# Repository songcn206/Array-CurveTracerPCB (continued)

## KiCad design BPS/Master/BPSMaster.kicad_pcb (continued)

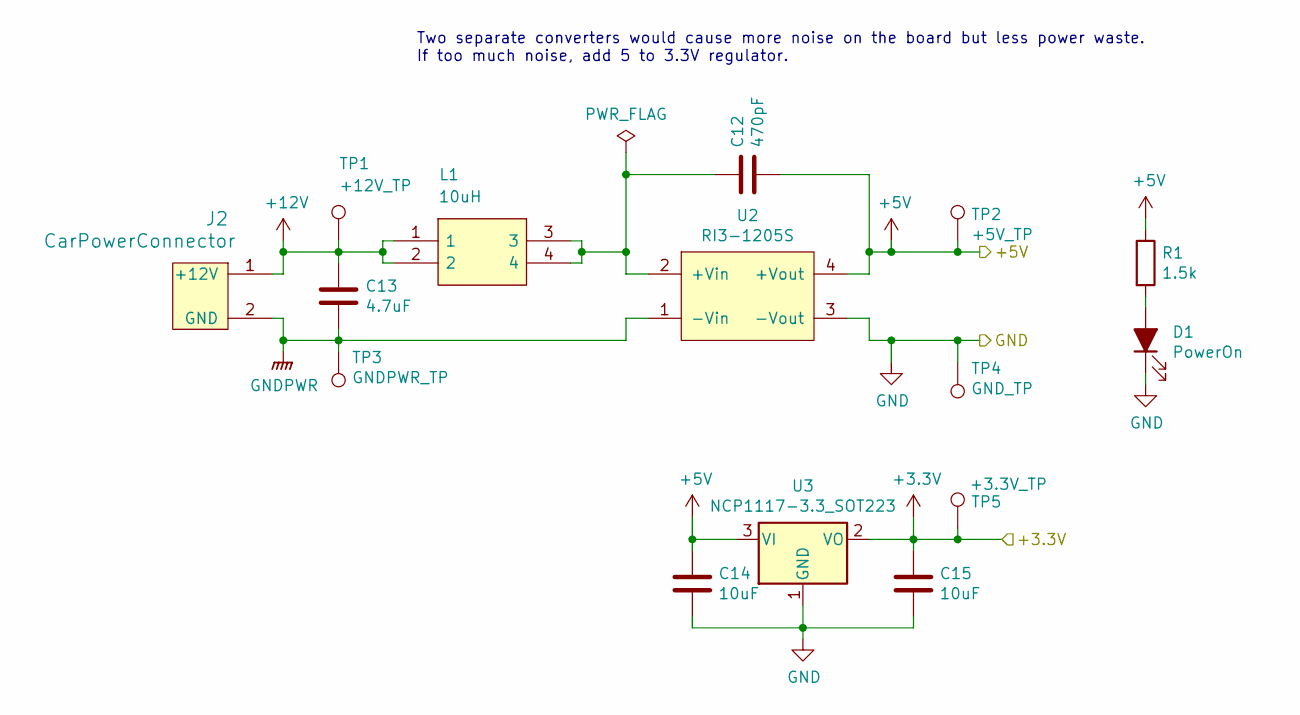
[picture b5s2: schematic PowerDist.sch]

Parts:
C12: 470pF; C_2220_5650Metric; Rating 4kV
C13: 4.7uF; C_0805_2012Metric
C14, C15: 10uF; C_0805_2012Metric
D1: PowerOn; LED_0805_2012Metric
J2: CarPowerConnector; Molex_MicroFit3.0_1x2xP3.00mm_PolarizingPeg_Vertical
L1: 10uH; SRF0905A
R1: 1.5k; R_0805_2012Metric
TP1: +12V_TP; TestPoint_Keystone_5005-5009_Compact
TP2: +5V_TP; TestPoint_Keystone_5005-5009_Compact
TP3: GNDPWR_TP; TestPoint_Keystone_5005-5009_Compact
TP4: GND_TP; TestPoint_Keystone_5005-5009_Compact
TP5: +3.3V_TP; TestPoint_Keystone_5005-5009_Compact
U2: RI3-1205S; RI3_DC_Converter
U3: NCP1117-3.3_SOT223; SOT-223-3_TabPin2

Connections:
+3V3: C15.1, TP5.1, U3.2 (VO); also elsewhere on the board
+5V: C12.2, C14.1, R1.1, TP2.1, U2.4 (+Vout), U3.3 (VI); also elsewhere on the board
+12V: C13.1, J2.1 (+12V), L1.1, L1.2, TP1.1; also elsewhere on the board
GND: C14.2, C15.2, D1.1 (K), TP4.1, U2.3 (-Vout), U3.1 (GND); also elsewhere on the board
GNDPWR: C13.2, J2.2 (GND), TP3.1, U2.1 (-Vin); also elsewhere on the board
unnamed: C12.1, L1.3, L1.4, U2.2 (+Vin)
unnamed: D1.2 (A), R1.2

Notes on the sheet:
Two separate converters would cause more noise on the board but less power waste. If too much noise, add 5 to 3.3V regulator.

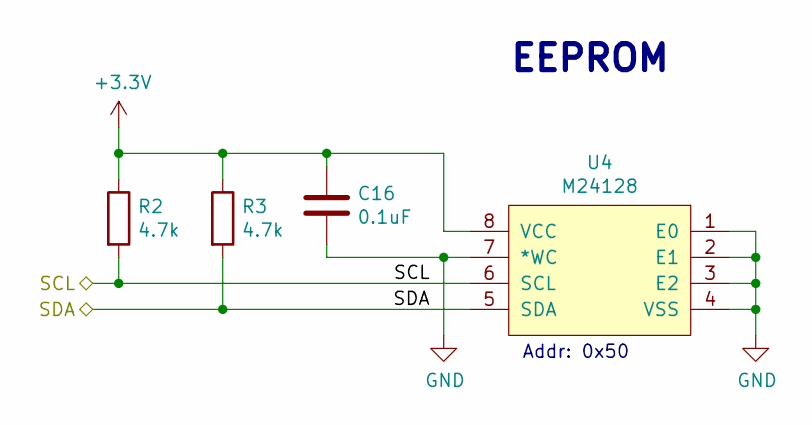
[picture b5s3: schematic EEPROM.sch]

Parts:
C16: 0.1uF; C_0805_2012Metric
R2, R3: 4.7k; R_0805_2012Metric
U4: M24128; M24128-BRMN6P

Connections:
+3V3: C16.1, R2.1, R3.1, U4.8 (VCC); also elsewhere on the board
/I2C3_SCL: R2.2, U4.6 (SCL); also elsewhere on the board
/I2C3_SDA: R3.2, U4.5 (SDA); also elsewhere on the board
GND: C16.2, U4.1 (E0), U4.2 (E1), U4.3 (E2), U4.4 (VSS), U4.7 (*WC); also elsewhere on the board

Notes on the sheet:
EEPROM
Addr: 0x50

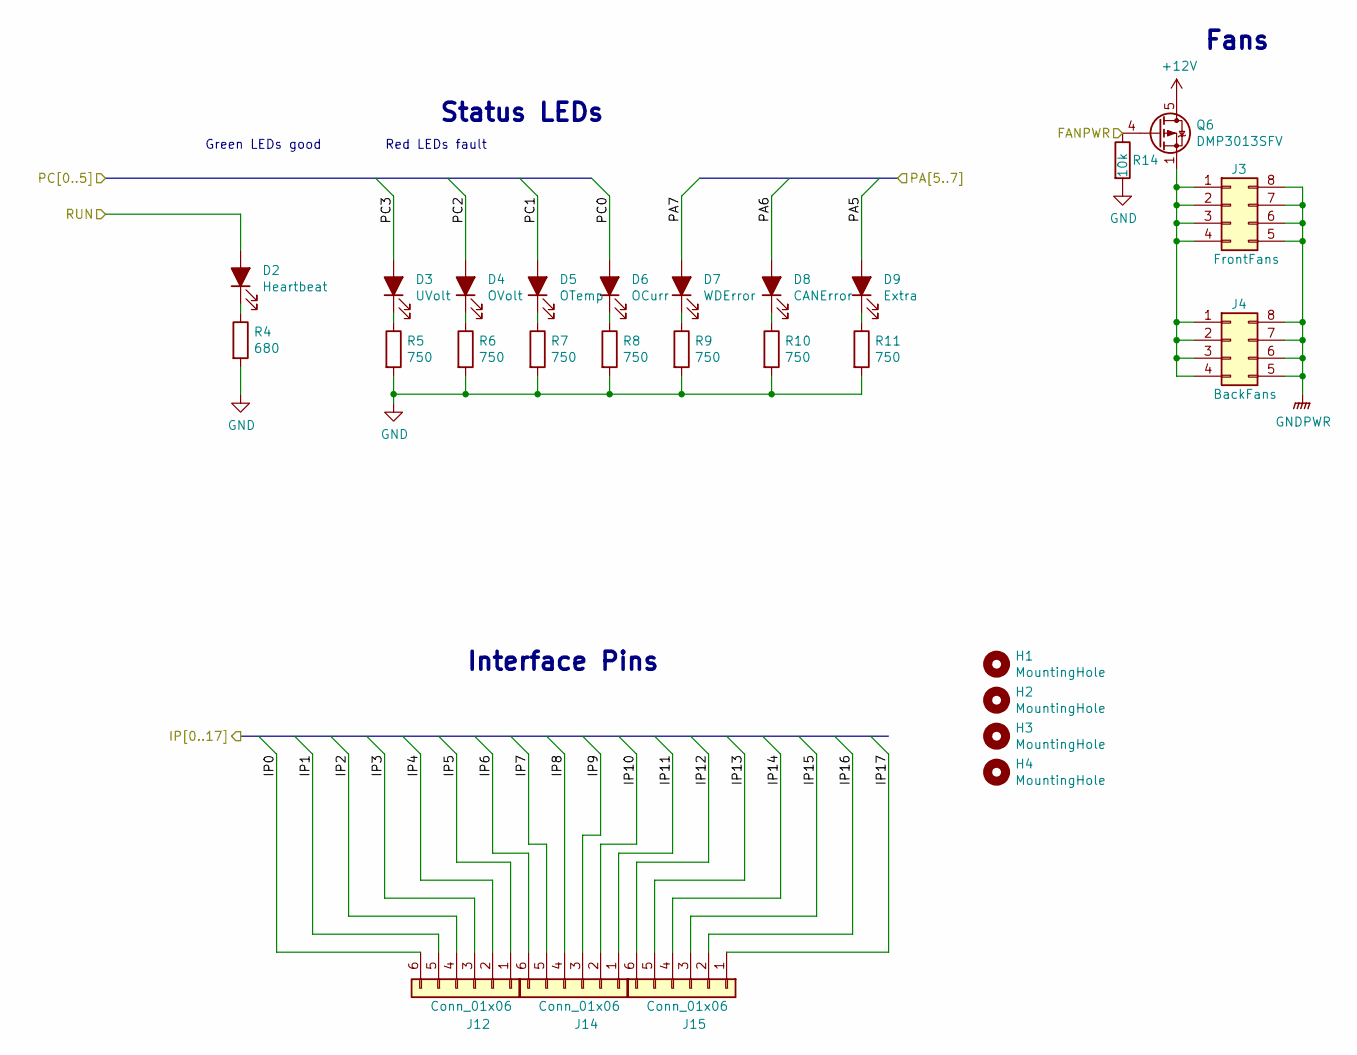
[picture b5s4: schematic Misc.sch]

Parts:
D2: Heartbeat; LED_0805_2012Metric
D3: UVolt; LED_0805_2012Metric
D4: OVolt; LED_0805_2012Metric
D5: OTemp; LED_0805_2012Metric
D6: OCurr; LED_0805_2012Metric
D7: WDError; LED_0805_2012Metric
D8: CANError; LED_0805_2012Metric
D9: Extra; LED_0805_2012Metric
H1, H2, H3, H4: MountingHole; MountingHole_2.1mm
J3: FrontFans; Molex_MicroFit3.0_2x4xP3.00mm_PolarizingPeg_Vertical
J4: BackFans; Molex_MicroFit3.0_2x4xP3.00mm_PolarizingPeg_Vertical
J12, J14, J15: Conn_01x06; PinHeader_1x06_P2.54mm_Vertical
Q6: DMP3013SFV; Diodes_PowerDI3333-8
R4: 680; R_0805_2012Metric
R5, R6, R7, R8, R9, R10, R11: 750; R_0805_2012Metric
R14: 10k; R_0805_2012Metric

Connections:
+12V: Q6.5 (D); also elsewhere on the board
/IP0: J12.6; also elsewhere on the board
/IP1: J12.5; also elsewhere on the board
/IP2: J12.4; also elsewhere on the board
/IP3: J12.3; also elsewhere on the board
/IP4: J12.2; also elsewhere on the board
/IP5: J12.1; also elsewhere on the board
/IP6: J14.6; also elsewhere on the board
/IP7: J14.5; also elsewhere on the board
/IP8: J14.4; also elsewhere on the board
/IP9: J14.3; also elsewhere on the board
/IP10: J14.2; also elsewhere on the board
/IP11: J14.1; also elsewhere on the board
/IP12: J15.6; also elsewhere on the board
/IP13: J15.5; also elsewhere on the board
/IP14: J15.4; also elsewhere on the board
/IP15: J15.3; also elsewhere on the board
/IP16: J15.2; also elsewhere on the board
/IP17: J15.1; also elsewhere on the board
/LPTIM1(PWM): Q6.4 (G), R14.1; also elsewhere on the board
/PA5: D9.2 (A); also elsewhere on the board
/PA6: D8.2 (A); also elsewhere on the board
/PA7: D7.2 (A); also elsewhere on the board
/PC0: D6.2 (A); also elsewhere on the board
/PC1: D5.2 (A); also elsewhere on the board
/PC2: D4.2 (A); also elsewhere on the board
/PC3: D3.2 (A); also elsewhere on the board
/RUN: D2.2 (A); also elsewhere on the board
GND: R4.2, R5.2, R6.2, R7.2, R8.2, R9.2, R10.2, R11.2, R14.2; also elsewhere on the board
GNDPWR: J3.5, J3.6, J3.7, J3.8, J4.5, J4.6, J4.7, J4.8; also elsewhere on the board
unnamed: D2.1 (K), R4.1
unnamed: D3.1 (K), R5.1
unnamed: D4.1 (K), R6.1
unnamed: D5.1 (K), R7.1
unnamed: D6.1 (K), R8.1
unnamed: D7.1 (K), R9.1
unnamed: D8.1 (K), R10.1
unnamed: D9.1 (K), R11.1
unnamed: J3.1, J3.2, J3.3, J3.4, J4.1, J4.2, J4.3, J4.4, Q6.1 (S), Q6.2 (S), Q6.3 (S)

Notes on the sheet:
Fans
Green LEDs good
Red LEDs fault
Status LEDs
Interface Pins

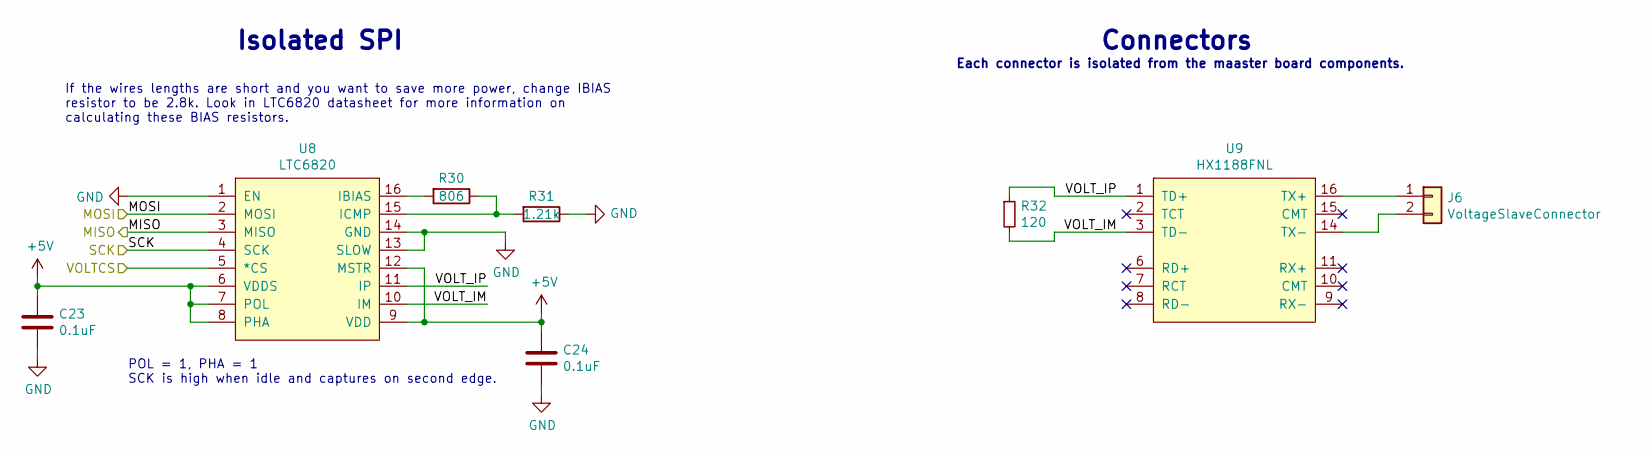
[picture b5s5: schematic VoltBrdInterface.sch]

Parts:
C23, C24: 0.1uF; C_0805_2012Metric
J6: VoltageSlaveConnector; Molex_MicroFit3.0_1x2xP3.00mm_PolarizingPeg_Vertical
R30: 806; R_0805_2012Metric
R31: 1.21k; R_0805_2012Metric
R32: 120; R_0805_2012Metric
U8: LTC6820; MSOP-16_3x4mm_P0.5mm
U9: HX1188FNL; HXXXX

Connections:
+5V: C23.1, C24.1, U8.6 (VDDS), U8.7 (POL), U8.8 (PHA), U8.9 (VDD), U8.12 (MSTR); also elsewhere on the board
/SPI1_CLK: U8.4 (SCK); also elsewhere on the board
/SPI1_MISO: U8.3 (MISO); also elsewhere on the board
/SPI1_MOSI: U8.2 (MOSI); also elsewhere on the board
/VOLT_CS: U8.5 (*CS); also elsewhere on the board
/Voltage Board Interface/VOLT_IM: R32.2, U8.10 (IM), U9.3 (TD-)
/Voltage Board Interface/VOLT_IP: R32.1, U8.11 (IP), U9.1 (TD+)
GND: C23.2, C24.2, R31.1, U8.1 (EN), U8.13 (SLOW), U8.14 (GND); also elsewhere on the board
unnamed: J6.1, U9.16 (TX+)
unnamed: J6.2, U9.14 (TX-)
unnamed: R30.1, R31.2, U8.15 (ICMP)
unnamed: R30.2, U8.16 (IBIAS)

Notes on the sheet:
POL = 1, PHA = 1 SCK is high when idle and captures on second edge.
If the wires lengths are short and you want to save more power, change IBIAS resistor to be 2.8k. Look in LTC6820 datasheet for more information on calculating these BIAS resistors.
Connectors
Each connector is isolated from the maaster board components.
Isolated SPI

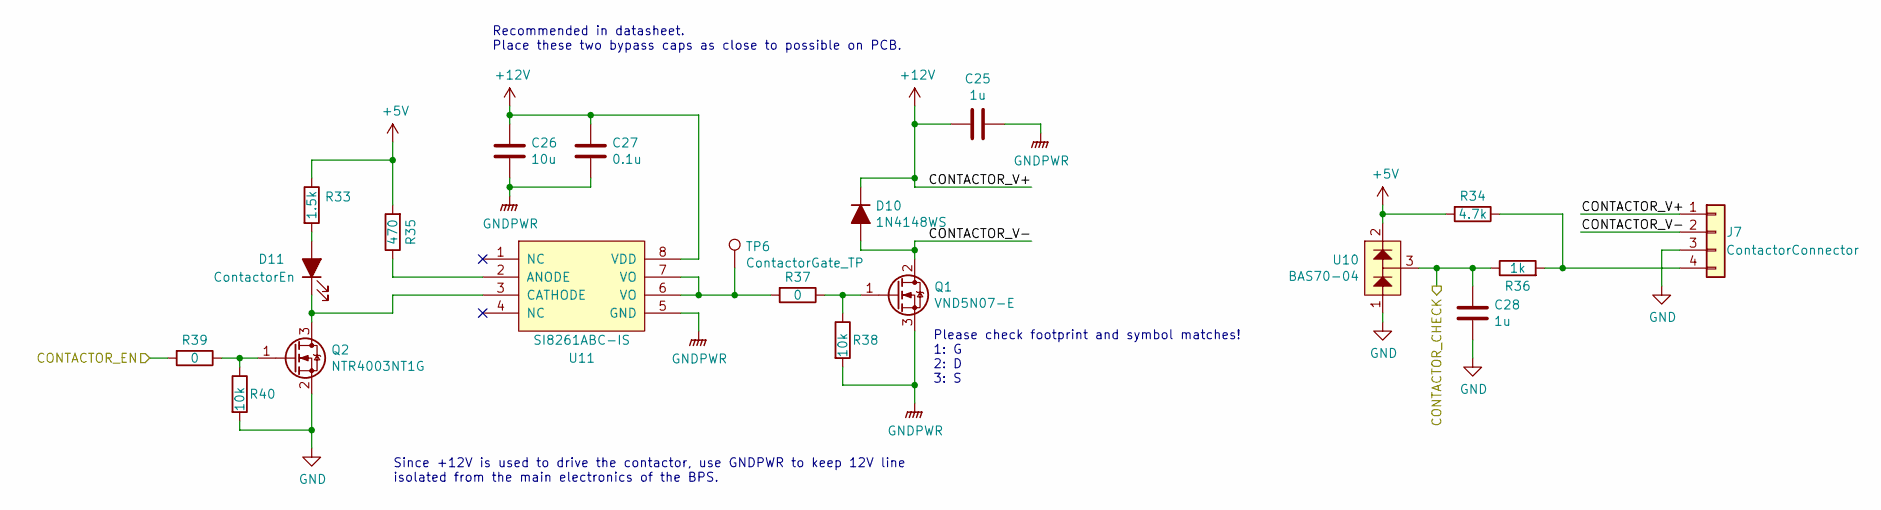
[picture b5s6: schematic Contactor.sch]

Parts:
C25, C28: 1u; C_0805_2012Metric
C26: 10u; C_0805_2012Metric
C27: 0.1u; C_0805_2012Metric
D10: 1N4148WS; D_SOD-323
D11: ContactorEn; LED_0805_2012Metric
J7: ContactorConnector; Molex_MicroFit3.0_1x4xP3.00mm_PolarizingPeg_Vertical
Q1: VND5N07-E; TO-252-2
Q2: NTR4003NT1G; SOT-23
R33: 1.5k; R_0805_2012Metric
R34: 4.7k; R_0805_2012Metric
R35: 470; R_0805_2012Metric
R36: 1k; R_0805_2012Metric
R37, R39: 0; R_0805_2012Metric
R38, R40: 10k; R_0805_2012Metric
TP6: ContactorGate_TP; TestPoint_Keystone_5005-5009_Compact
U10: BAS70-04; SOT-23
U11: SI8261ABC-IS; SOIC-8_3.9x4.9mm_P1.27mm

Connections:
+5V: R33.1, R34.2, R35.2, U10.2; also elsewhere on the board
+12V: C25.2, C26.1, C27.1, D10.1 (K), J7.1, U11.8 (VDD); also elsewhere on the board
/Contactor Driver/CONTACTOR_V-: D10.2 (A), J7.2, Q1.2 (D)
/PB0: R39.2; also elsewhere on the board
/PB1: C28.1, R36.1, U10.3; also elsewhere on the board
GND: C28.2, J7.3, Q2.2 (S), R40.2, U10.1; also elsewhere on the board
GNDPWR: C25.1, C26.2, C27.2, Q1.3 (S), R38.2, U11.5 (GND); also elsewhere on the board
unnamed: D11.1 (K), Q2.3 (D), U11.3 (CATHODE)
unnamed: D11.2 (A), R33.2
unnamed: J7.4, R34.1, R36.2
unnamed: Q1.1 (G), R37.1, R38.1
unnamed: Q2.1 (G), R39.1, R40.1
unnamed: R35.1, U11.2 (ANODE)
unnamed: R37.2, TP6.1, U11.6 (VO), U11.7 (VO)

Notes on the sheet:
Since +12V is used to drive the contactor, use GNDPWR to keep 12V line isolated from the main electronics of the BPS.
Recommended in datasheet. Place these two bypass caps as close to possible on PCB.
Please check footprint and symbol matches! 1: G 2: D 3: S

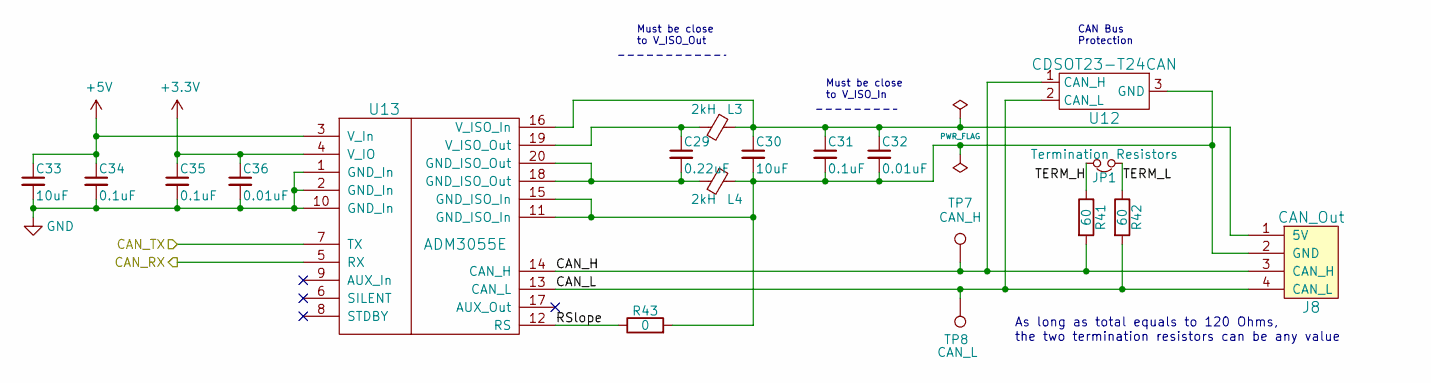
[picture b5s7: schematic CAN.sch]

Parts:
C29: 0.22uF; C_0805_2012Metric
C30, C33: 10uF; C_0805_2012Metric
C31, C34, C35: 0.1uF; C_0805_2012Metric
C32, C36: 0.01uF; C_0805_2012Metric
J8: CAN_Out; Molex_MicroFit3.0_1x4xP3.00mm_PolarizingPeg_Vertical
JP1: Termination Resistors; PinHeader_1x02_P2.54mm_Vertical
L3, L4: 2kH; L_0805_2012Metric
R41, R42: 60; R_0805_2012Metric
R43: 0; R_0805_2012Metric
TP7: CAN_H; TestPoint_Keystone_5005-5009_Compact
TP8: CAN_L; TestPoint_Keystone_5005-5009_Compact
U12: CDSOT23-T24CAN; SOT-23W
U13: ADM3055E; SOIC-20W_7.5x15.4mm_Pitch1.27mm

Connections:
+3V3: C35.1, C36.1, U13.4 (V_IO); also elsewhere on the board
+5V: C33.1, C34.1, U13.3 (V_In); also elsewhere on the board
/CAN1_RX: U13.5 (RX); also elsewhere on the board
/CAN1_TX: U13.7 (TX); also elsewhere on the board
/CAN/CAN_H: J8.3 (CAN_H), R41.2, TP7.1, U12.1 (CAN_H), U13.14 (CAN_H)
/CAN/CAN_L: J8.4 (CAN_L), R42.2, TP8.1, U12.2 (CAN_L), U13.13 (CAN_L)
/CAN/RSlope: R43.1, U13.12 (RS)
/CAN/TERM_H: JP1.2, R41.1
/CAN/TERM_L: JP1.1, R42.1
GND: C33.2, C34.2, C35.2, C36.2, U13.1 (GND_In), U13.2 (GND_In), U13.10 (GND_In); also elsewhere on the board
unnamed: C29.1, L3.2, U13.19 (V_ISO_Out)
unnamed: C29.2, L4.2, U13.18 (GND_ISO_Out), U13.20 (GND_ISO_Out)
unnamed: C30.1, C31.1, C32.1, J8.1 (5V), L3.1, U13.16 (V_ISO_In)
unnamed: C30.2, C31.2, C32.2, J8.2 (GND), L4.1, R43.2, U12.3 (GND), U13.11 (GND_ISO_In), U13.15 (GND_ISO_In)

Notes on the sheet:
Must be close to V_ISO_Out
Must be close to V_ISO_In
CAN Bus Protection
As long as total equals to 120 Ohms, the two termination resistors can be any value

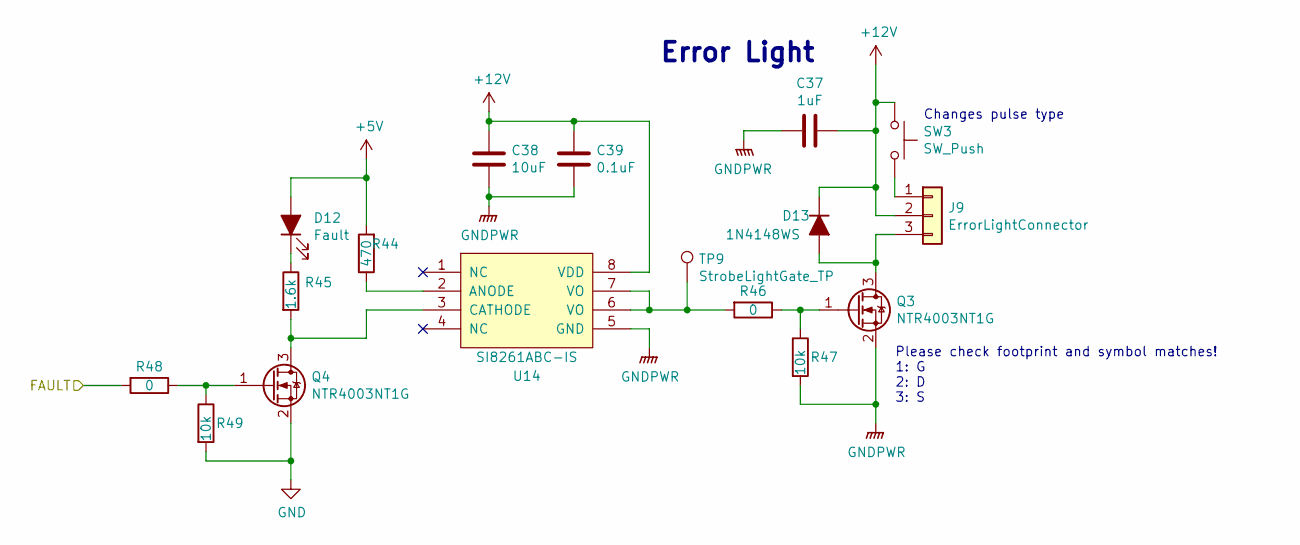
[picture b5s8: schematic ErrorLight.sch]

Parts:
C37: 1uF; C_0805_2012Metric
C38: 10uF; C_0805_2012Metric
C39: 0.1uF; C_0805_2012Metric
D12: Fault; LED_0805_2012Metric
D13: 1N4148WS; D_SOD-323
J9: ErrorLightConnector; Molex_MicroFit3.0_1x3xP3.00mm_PolarizingPeg_Vertical
Q3, Q4: NTR4003NT1G; SOT-23
R44: 470; R_0805_2012Metric
R45: 1.6k; R_0805_2012Metric
R46, R48: 0; R_0805_2012Metric
R47, R49: 10k; R_0805_2012Metric
SW3: SW_Push; SW_SPST_B3SL-1002P
TP9: StrobeLightGate_TP; TestPoint_Keystone_5005-5009_Compact
U14: SI8261ABC-IS; SOIC-8_3.9x4.9mm_P1.27mm

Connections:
+5V: D12.2 (A), R44.2; also elsewhere on the board
+12V: C37.2, C38.1, C39.1, D13.1 (K), J9.2, SW3.1, U14.8 (VDD); also elsewhere on the board
/FAULT: R48.2; also elsewhere on the board
GND: Q4.2 (S), R49.2; also elsewhere on the board
GNDPWR: C37.1, C38.2, C39.2, Q3.2 (S), R47.2, U14.5 (GND); also elsewhere on the board
unnamed: D12.1 (K), R45.1
unnamed: D13.2 (A), J9.3, Q3.3 (D)
unnamed: J9.1, SW3.2
unnamed: Q3.1 (G), R46.1, R47.1
unnamed: Q4.1 (G), R48.1, R49.1
unnamed: Q4.3 (D), R45.2, U14.3 (CATHODE)
unnamed: R44.1, U14.2 (ANODE)
unnamed: R46.2, TP9.1, U14.6 (VO), U14.7 (VO)

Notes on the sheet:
Error Light
Please check footprint and symbol matches! 1: G 2: D 3: S
Changes pulse type

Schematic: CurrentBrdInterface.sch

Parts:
C40: 0.1uF; C_0805_2012Metric
C41, C42: 0.01u; C_0805_2012Metric
J10: CurrentSlaveConnector; Molex_MicroFit3.0_1x4xP3.00mm_PolarizingPeg_Vertical
L5, L6: 600; L_0805_2012Metric
R12, R13, R50, R51: 100; R_0805_2012Metric
U5: LTC6256; LTC6256CTS8-TRMPBF

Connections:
+3V3: R12.2, R13.2, U5.8 (V+); also elsewhere on the board
+5V: C40.2, J10.1; also elsewhere on the board
/ADC1_CH2: C41.1, R51.2; also elsewhere on the board
/ADC1_CH3: C42.2, R50.2; also elsewhere on the board
GND: C40.1, C41.2, C42.1, J10.2, U5.4 (V-); also elsewhere on the board
unnamed: J10.3, L5.1
unnamed: J10.4, L6.1
unnamed: L5.2, R12.1, U5.3 (+INA)
unnamed: L6.2, R13.1, U5.5 (+INB)
unnamed: R50.1, U5.1 (OUTA), U5.2 (-INA)
unnamed: R51.1, U5.6 (-INB), U5.7 (OUTB)

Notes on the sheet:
PA2 high precision hall effect sensor. PA3 low precision hall effect sensor.
Current Board
The ADC has low impedence so buffer op-amp will prevent weird measurement deviations.
Pull up resistors are for disconnections

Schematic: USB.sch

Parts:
C43: 4.7uF; C_0805_2012Metric
C44: 0.1uF; C_0805_2012Metric
D14: SP0503BAHT; SOT-143
J11: USB_B_Micro; USB_Micro-B_Molex-105017-0001
R52: 1k; R_0805_2012Metric
R53: 22.1k; R_0805_2012Metric
R54: 47.5k; R_0805_2012Metric
U15: CP2102N-A01-GQFN24; QFN-24-1EP_4x4mm_P0.5mm_EP2.6x2.6mm

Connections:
+3V3: C43.1, C44.1, R52.1, U15.5 (VIO), U15.6 (VDD), U15.7 (REGIN); also elsewhere on the board
/USART3_RX: U15.21 (TXD); also elsewhere on the board
/USART3_TX: U15.20 (RXD); also elsewhere on the board
GND: C43.2, C44.2, D14.1 (A), J11.5 (GND), J11.6 (Shield), R54.2, U15.2 (GND), U15.25 (GND); also elsewhere on the board
unnamed: D14.2 (K), J11.1 (VBUS), R53.2
unnamed: D14.3 (K), J11.2 (D-), U15.4 (D-)
unnamed: D14.4 (K), J11.3 (D+), U15.3 (D+)
unnamed: R52.2, U15.9 (~RSTb)
unnamed: R53.1, R54.1, U15.8 (VBUS)

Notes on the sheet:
The microcontroller should have Rx connected to UART_TX and Tx connected to UART_RX

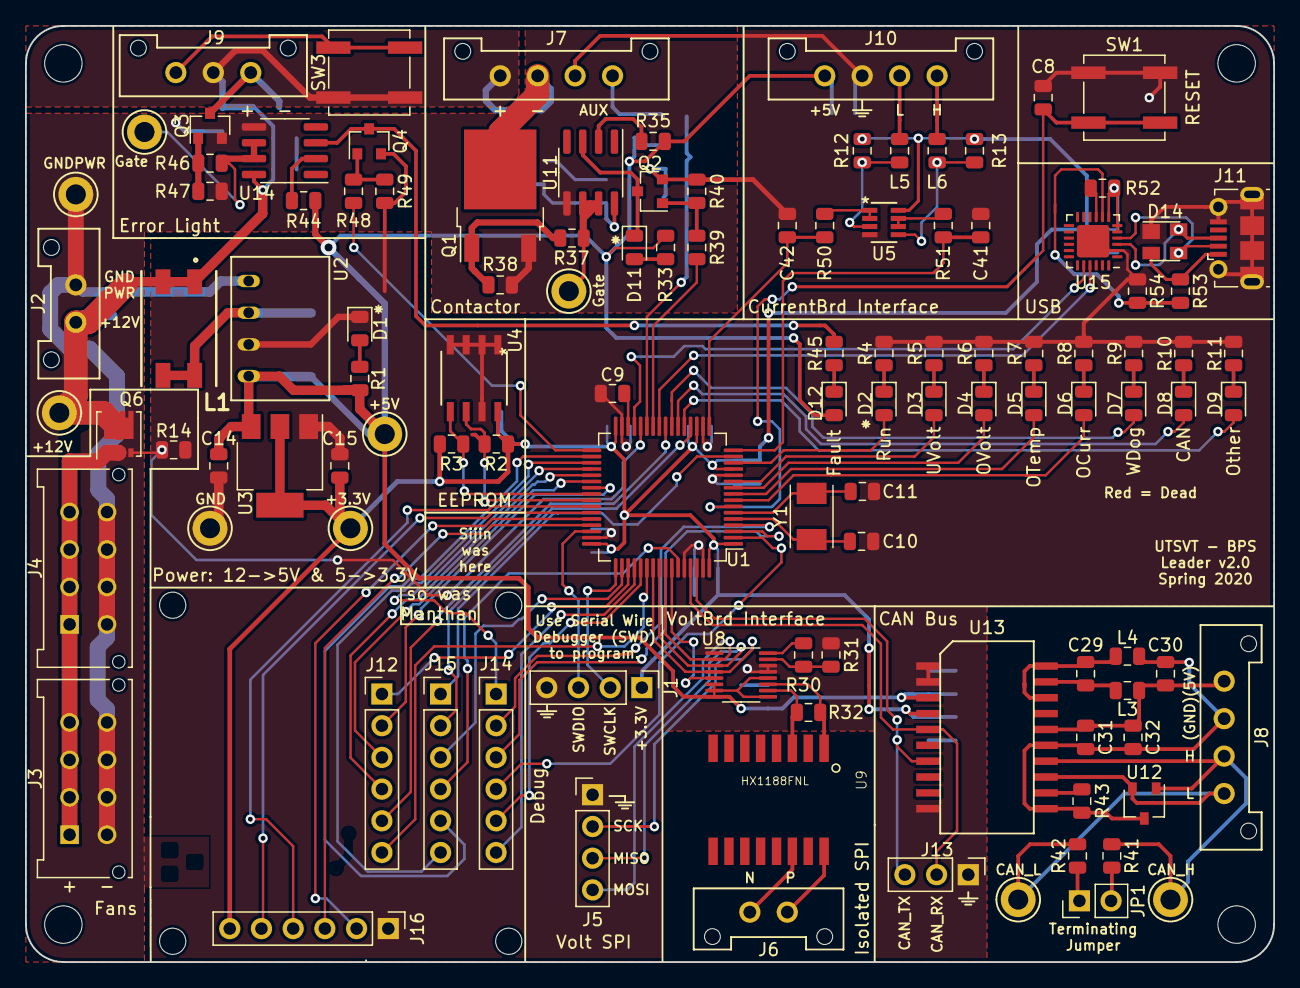
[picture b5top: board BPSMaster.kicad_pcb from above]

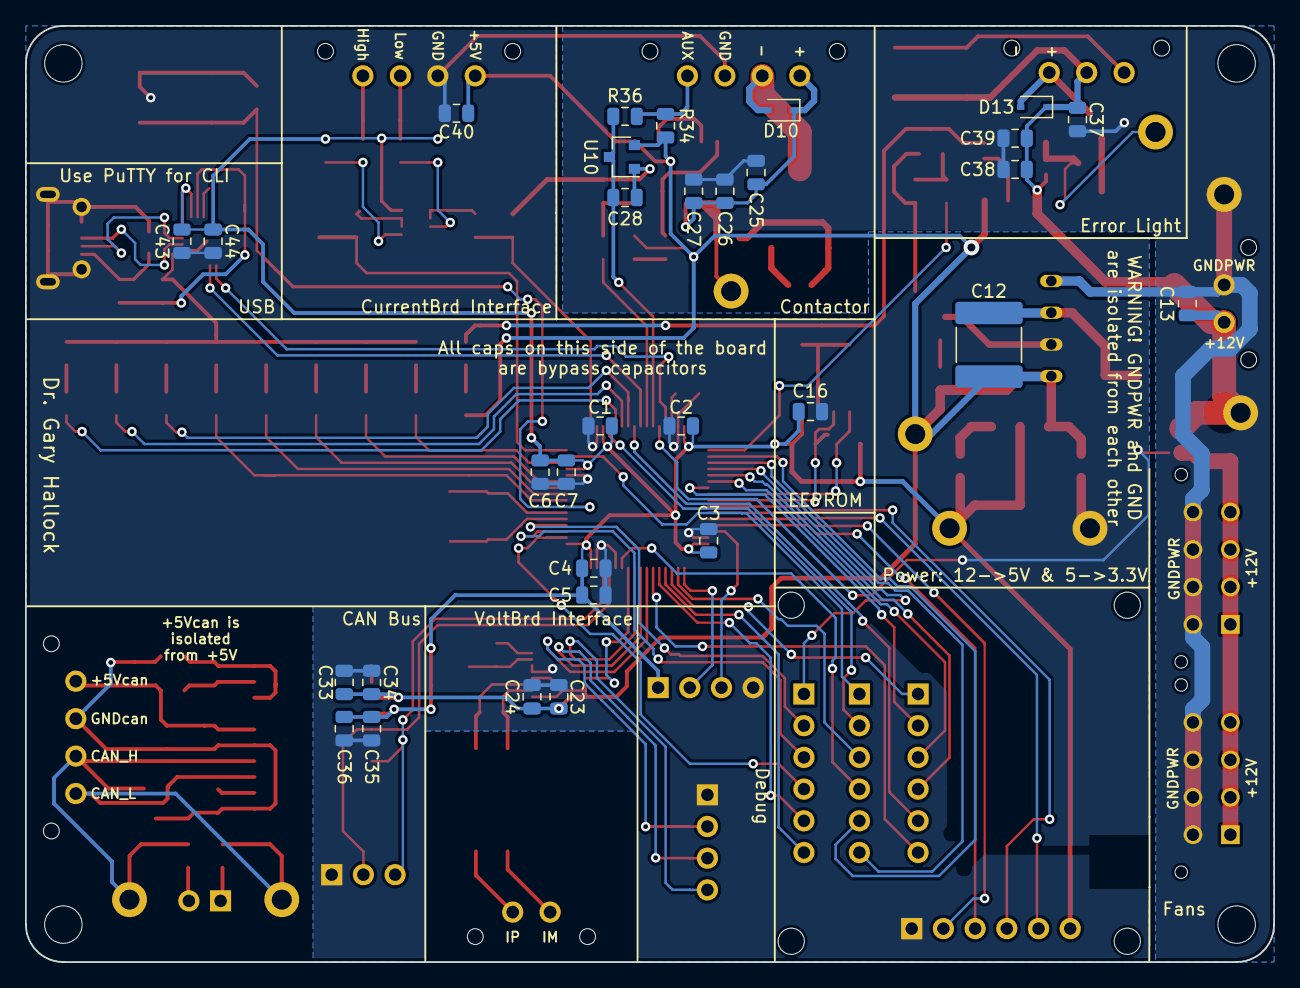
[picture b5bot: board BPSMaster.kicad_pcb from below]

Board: 2 copper layers, 100.0 x 75.0 mm, 151 parts (31 on the bottom side), 110 nets.

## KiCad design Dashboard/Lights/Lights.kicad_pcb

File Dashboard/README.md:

# Dashboard 2.0

This design of the dashboard uses a single unified
PCB for the dashboard and motor interface functions. 

## Overview
This dashboard contains
* Two CAN bus interfaces.
* A USB interface for MCU-Computer UART comms.
* A UART interface for communication with the Gecko board.
* A JTAG programming interface.
* Multiple potentiometer/analog interfaces.
* Several LED drivers.
* Several switch inputs.
* Onboard voltage regulation from a 12V source.
* Ignition-switch style dial for activation.
* Hardware ticker to simplify operation of the turn indicators.

## Pin Configuration
Right now, the pins are configured as:

Pin  | Function                | Input / Output
-----|-------------------------|---------------
PA0  | Brake Light             | Output
PA1  |                         |
PA2  | USART2 TX (Gecko)       | 
PA3  | USART2 RX (Gecko}       |
PA4  |                         | 
PA5  |                         |
PA6  |                         |
PA7  |                         |
PA8  |                         | 
PA9  |                         | 
PA10 |                         |
PA11 | Car CAN RX              |
PA12 | Car CAN TX              |
PA13 | SWDIO (Programming)     |
PA14 | SWCLK (Programming)     |
PA15 | JTDI  (Programming)     |
PB0  | Headlights              | Input
PB1  | Right Turn Switch       | Input
PB2  | Left Turn Switch        | Input
PB3  | JTDO (Programming)      |
PB4  | Motor Precharge         | Output
PB5  | Motor Contactor         | Output
PB6  | Array Precharge         | Output
PB7  | Array Contactor         | Output
PB8  | Forward/Reverse Switch  | Output
PB9  |                         |
PB10 | USB TX                  |
PB11 |_Does not actually exist_| 
PB12 | Motor CAN RX            |
PB13 | Motor CAN TX            |
PB14 | Ignition Switch 1       | Input
PB15 | Ignition Switch 2       | Input
PC0  | Accelerator Pot.        | Analog Input
PC1  | Brake Pot.              | Analog Input
PC2  |                         | 
PC3  |                         | 
PC4  |                         |
PC5  | USB RX                  |
PC6  |                         |
PC7  |                         |
PC8  |                         |
PC9  |                         |
PC10 |                         |
PC11 | BPS Fault LED           | Output
PC12 | Control Fault LED       | Output
PC13 | Reserved LED            | Output
PC14 | Cruise Enable           | Input
PC15 | Cruise Set              | Input
PD2  |                         |

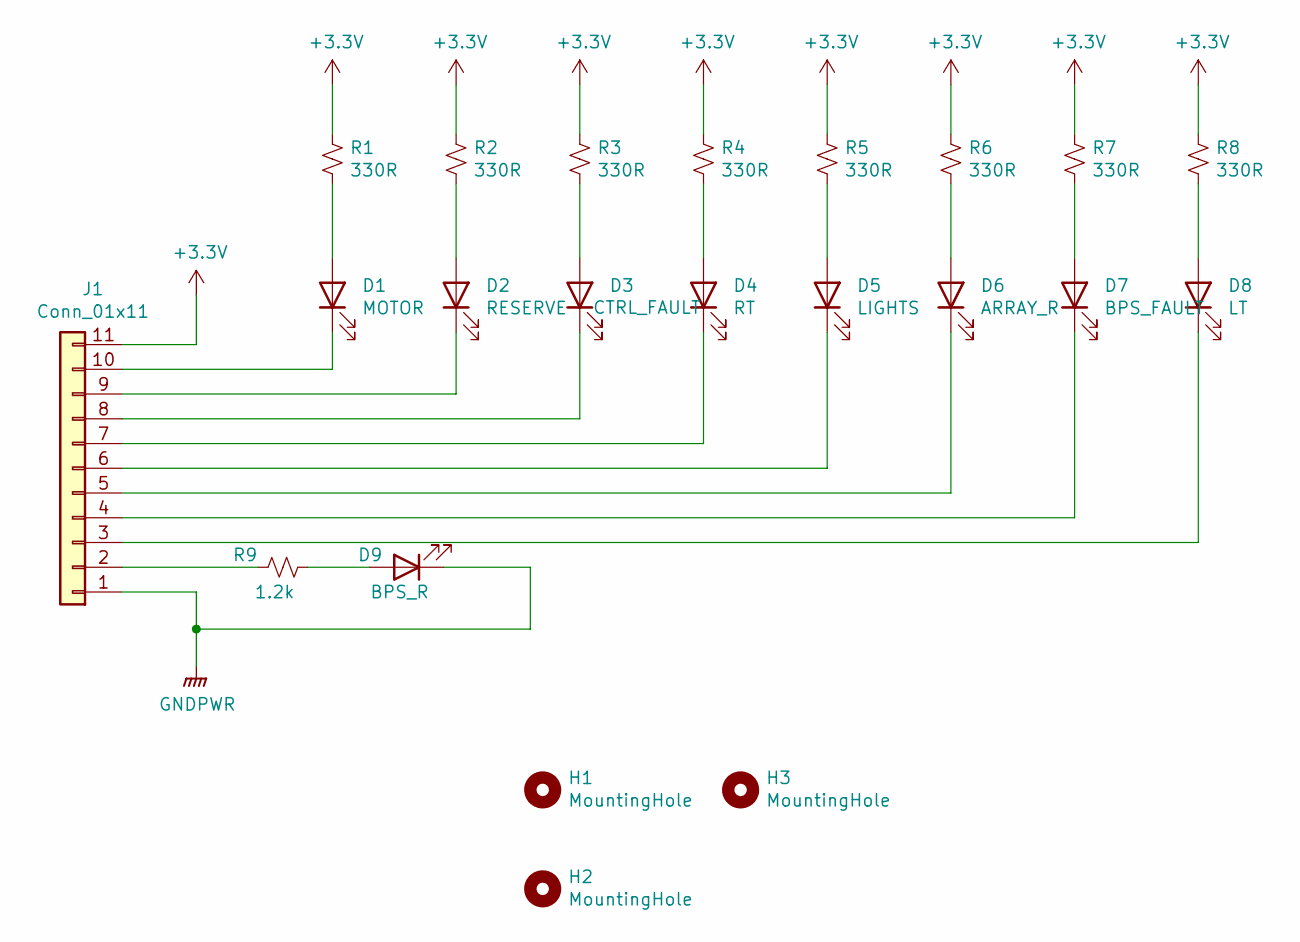
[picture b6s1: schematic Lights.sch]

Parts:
D1: MOTOR; LED_0805_2012Metric
D2: RESERVE; LED_0805_2012Metric
D3: CTRL_FAULT; LED_0805_2012Metric
D4: RT; LED_0805_2012Metric
D5: LIGHTS; LED_0805_2012Metric
D6: ARRAY_R; LED_0805_2012Metric
D7: BPS_FAULT; LED_0805_2012Metric
D8: LT; LED_0805_2012Metric
D9: BPS_R; LED_0805_2012Metric
H1, H2, H3: MountingHole; MountingHole_3mm
J1: Conn_01x11; PinHeader_2x07_P2.54mm_Vertical
R1, R2, R3, R4, R5, R6, R7, R8: 330R; R_0805_2012Metric
R9: 1.2k; R_0805_2012Metric

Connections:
+3V3: J1.11, R1.1, R2.1, R3.1, R4.1, R5.1, R6.1, R7.1, R8.1
GNDPWR: D9.1 (K), J1.1
unnamed: D1.1 (K), J1.10
unnamed: D1.2 (A), R1.2
unnamed: D2.1 (K), J1.9
unnamed: D2.2 (A), R2.2
unnamed: D3.1 (K), J1.8
unnamed: D3.2 (A), R3.2
unnamed: D4.1 (K), J1.7
unnamed: D4.2 (A), R4.2
unnamed: D5.1 (K), J1.6
unnamed: D5.2 (A), R5.2
unnamed: D6.1 (K), J1.5
unnamed: D6.2 (A), R6.2
unnamed: D7.1 (K), J1.4
unnamed: D7.2 (A), R7.2
unnamed: D8.1 (K), J1.3
unnamed: D8.2 (A), R8.2
unnamed: D9.2 (A), R9.2
unnamed: J1.2, R9.1

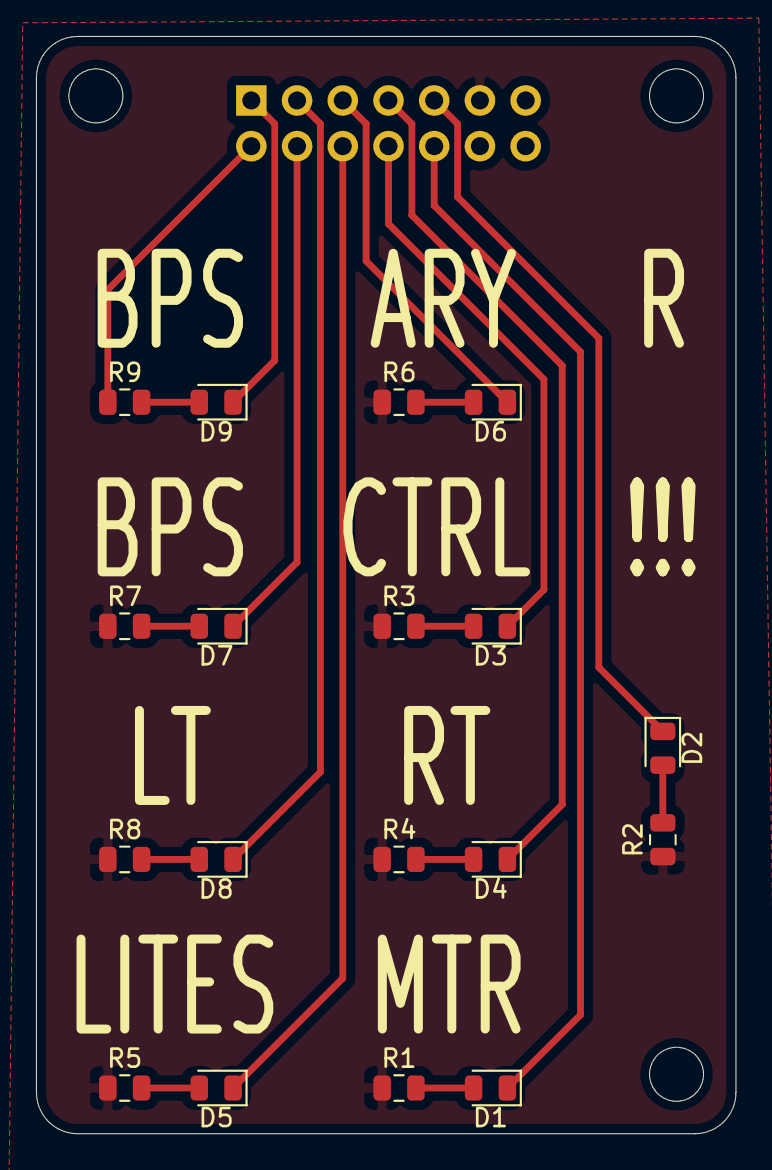
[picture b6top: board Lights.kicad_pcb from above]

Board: 2 copper layers, 38.9 x 61.0 mm, 22 parts (1 on the bottom side), 20 nets.
